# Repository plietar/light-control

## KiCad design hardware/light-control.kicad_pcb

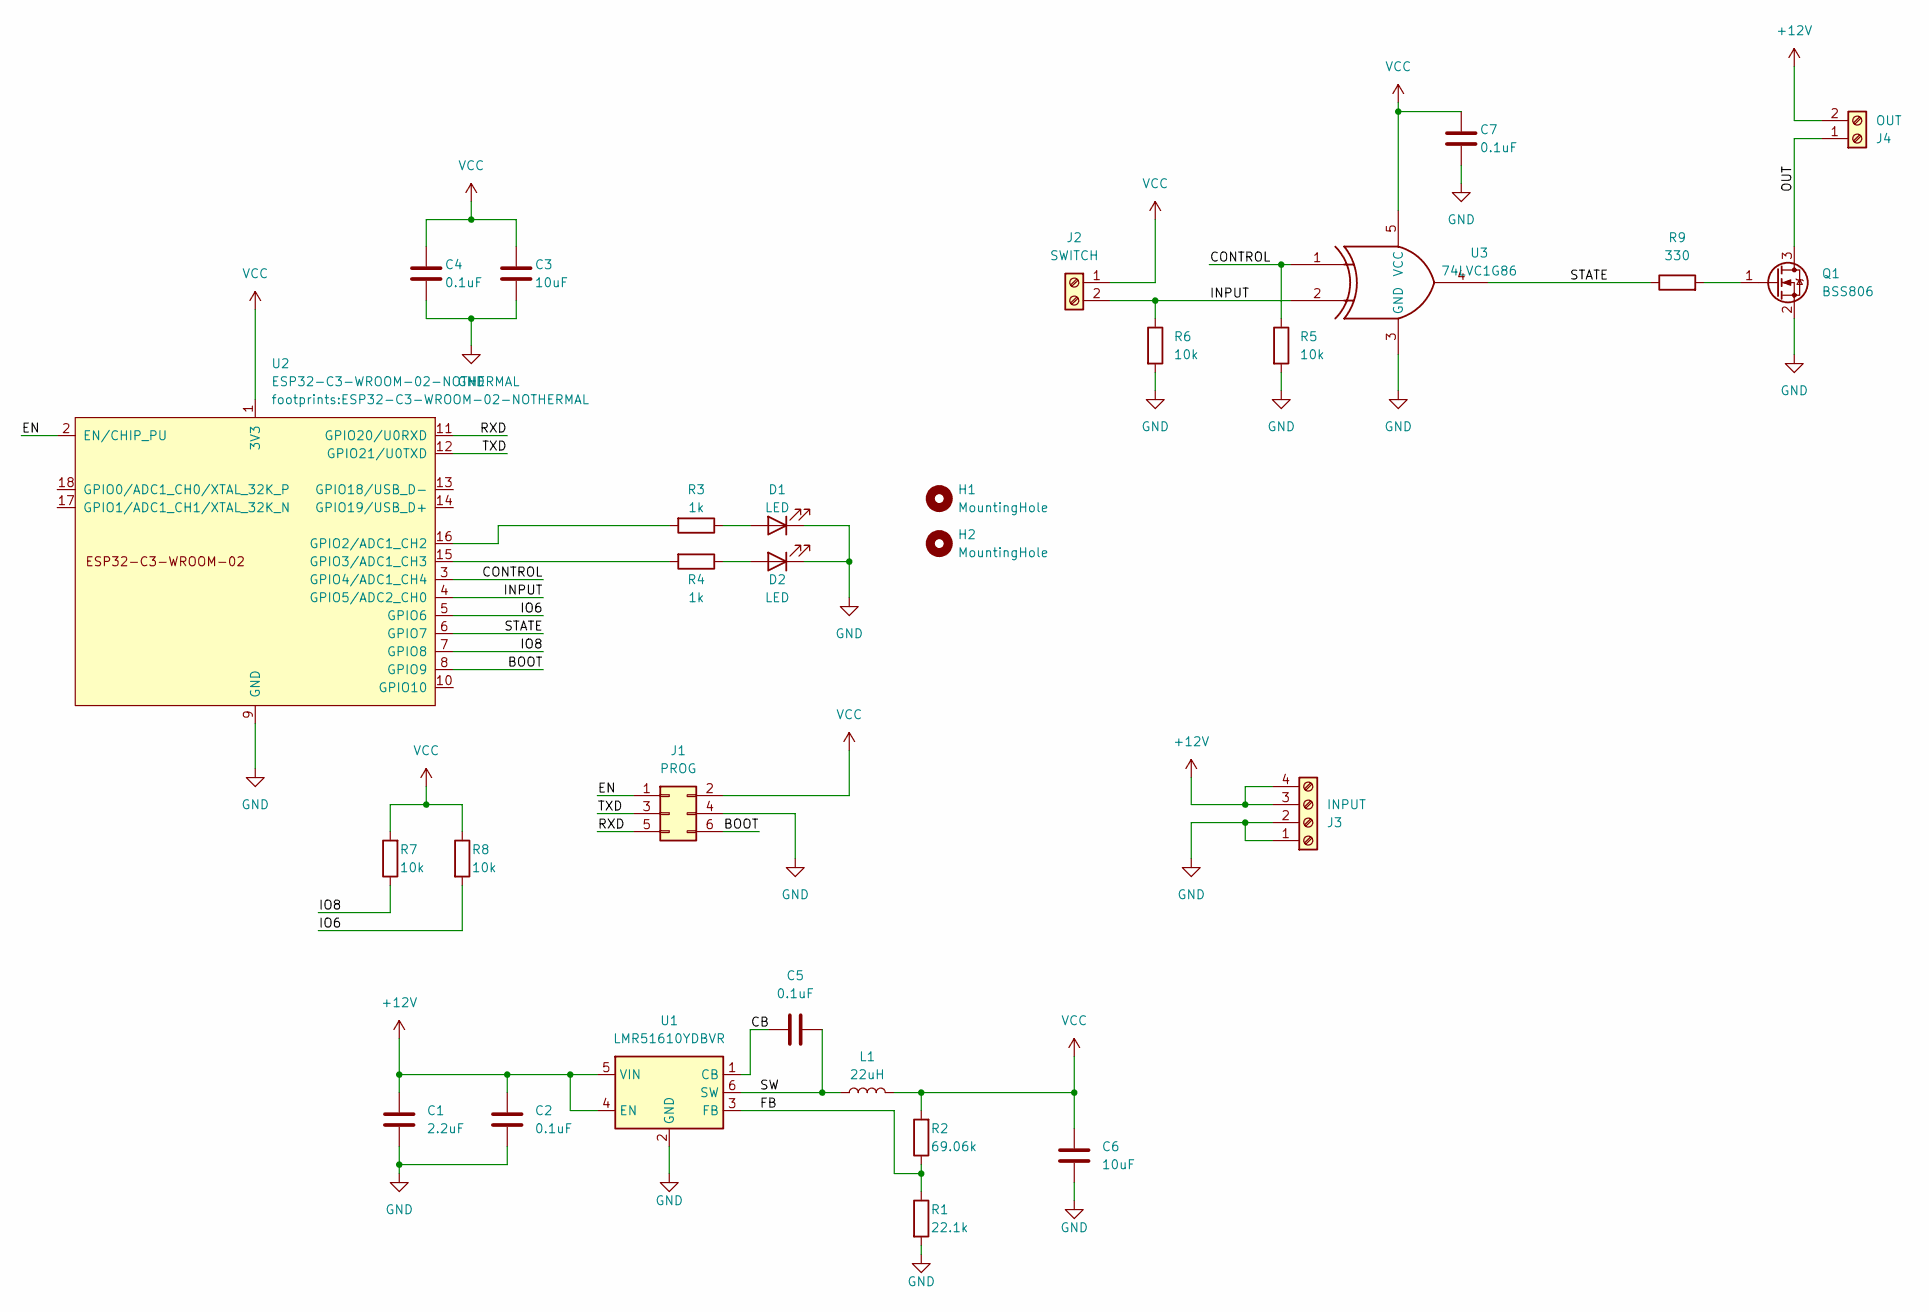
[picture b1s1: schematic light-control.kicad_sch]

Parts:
C1: 2.2uF; C_1206_3216Metric_Pad1.33x1.80mm_HandSolder
C2, C4, C5, C7: 0.1uF; C_1206_3216Metric_Pad1.33x1.80mm_HandSolder
C3: 10uF; C_1206_3216Metric_Pad1.33x1.80mm_HandSolder
C6: 10uF; C_1210_3225Metric_Pad1.33x2.70mm_HandSolder
D1, D2: LED; LED_1206_3216Metric_Pad1.42x1.75mm_HandSolder
H1, H2: MountingHole; MountingHole_2.2mm_M2
J1: PROG; Tag-Connect_TC2030-IDC-NL_2x03_P1.27mm_Vertical
J2: SWITCH; TerminalBlock_Phoenix_PT-1,5-2-3.5-H_1x02_P3.50mm_Horizontal
J3: INPUT; TerminalBlock_Phoenix_PT-1,5-4-3.5-H_1x04_P3.50mm_Horizontal
J4: OUT; TerminalBlock_Phoenix_PT-1,5-2-3.5-H_1x02_P3.50mm_Horizontal
L1: 22uH; L_TDK_VLS6045EX_VLS6045AF; Part number VLS6045EX-220M
Q1: BSS806; SOT-23_Handsoldering
R1: 22.1k; R_1206_3216Metric_Pad1.30x1.75mm_HandSolder
R2: 69.06k; R_1206_3216Metric_Pad1.30x1.75mm_HandSolder
R3, R4: 1k; R_1206_3216Metric_Pad1.30x1.75mm_HandSolder
R5, R6, R7, R8: 10k; R_1206_3216Metric_Pad1.30x1.75mm_HandSolder
R9: 330; R_1206_3216Metric_Pad1.30x1.75mm_HandSolder
U1: LMR51610YDBVR; SOT-23-6
U2: ESP32-C3-WROOM-02-NOTHERMAL
U3: 74LVC1G86; SOT-23-5_HandSoldering

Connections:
+12V: C1.1, C2.1, J3.3, J3.4, J4.2, U1.4 (EN), U1.5 (VIN)
/BOOT: J1.6, U2.8 (GPIO9)
/CB: C5.1, U1.1 (CB)
/CONTROL: R5.1, U2.3 (GPIO4/ADC1_CH4), U3.1
/EN: J1.1, U2.2 (EN/CHIP_PU)
/FB: R1.1, R2.1, U1.3 (FB)
/INPUT: J2.2, R6.1, U2.4 (GPIO5/ADC2_CH0), U3.2
/IO6: R8.2, U2.5 (GPIO6)
/IO8: R7.1, U2.7 (GPIO8)
/OUT: J4.1, Q1.3 (D)
/RXD: J1.5, U2.11 (GPIO20/U0RXD)
/STATE: R9.1, U2.6 (GPIO7), U3.4
/SW: C5.2, L1.1, U1.6 (SW)
/TXD: J1.3, U2.12 (GPIO21/U0TXD)
GND: C1.2, C2.2, C3.2, C4.2, C6.2, C7.2, D1.1 (K), D2.1 (K), J1.4, J3.1, J3.2, Q1.2 (S), R1.2, R5.2, R6.2, U1.2 (GND), U2.9 (GND), U3.3 (GND)
unnamed: D1.2 (A), R3.1
unnamed: D2.2 (A), R4.1
unnamed: Q1.1 (G), R9.2
unnamed: R3.2, U2.16 (GPIO2/ADC1_CH2)
unnamed: R4.2, U2.15 (GPIO3/ADC1_CH3)
VCC: C3.1, C4.1, C6.1, C7.1, J1.2, J2.1, L1.2, R2.2, R7.2, R8.1, U2.1 (3V3), U3.5 (VCC)

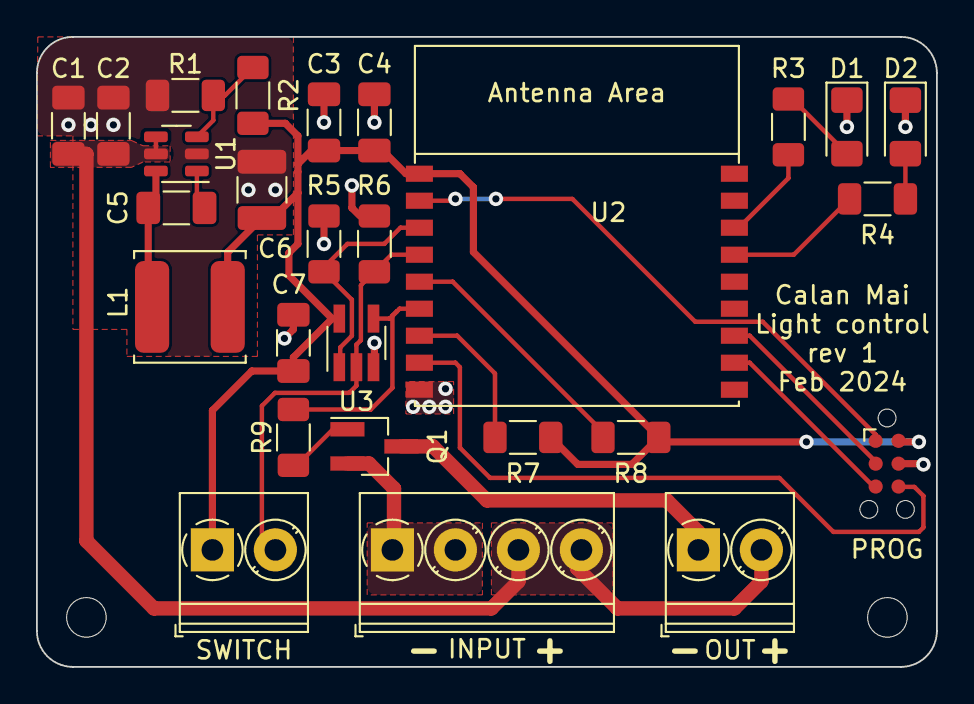
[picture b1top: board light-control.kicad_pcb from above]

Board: 2 copper layers, 50.0 x 35.0 mm, 29 parts (0 on the bottom side), 21 nets.

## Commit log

2024-03-03 Initial hardware revision
2024-10-11 Initial firmware version
2024-10-11 Add new device
2024-10-11 Show build logs
2024-10-11 Use prebuilt toolchain on CI.
2024-10-11 Render schematics on CI.
